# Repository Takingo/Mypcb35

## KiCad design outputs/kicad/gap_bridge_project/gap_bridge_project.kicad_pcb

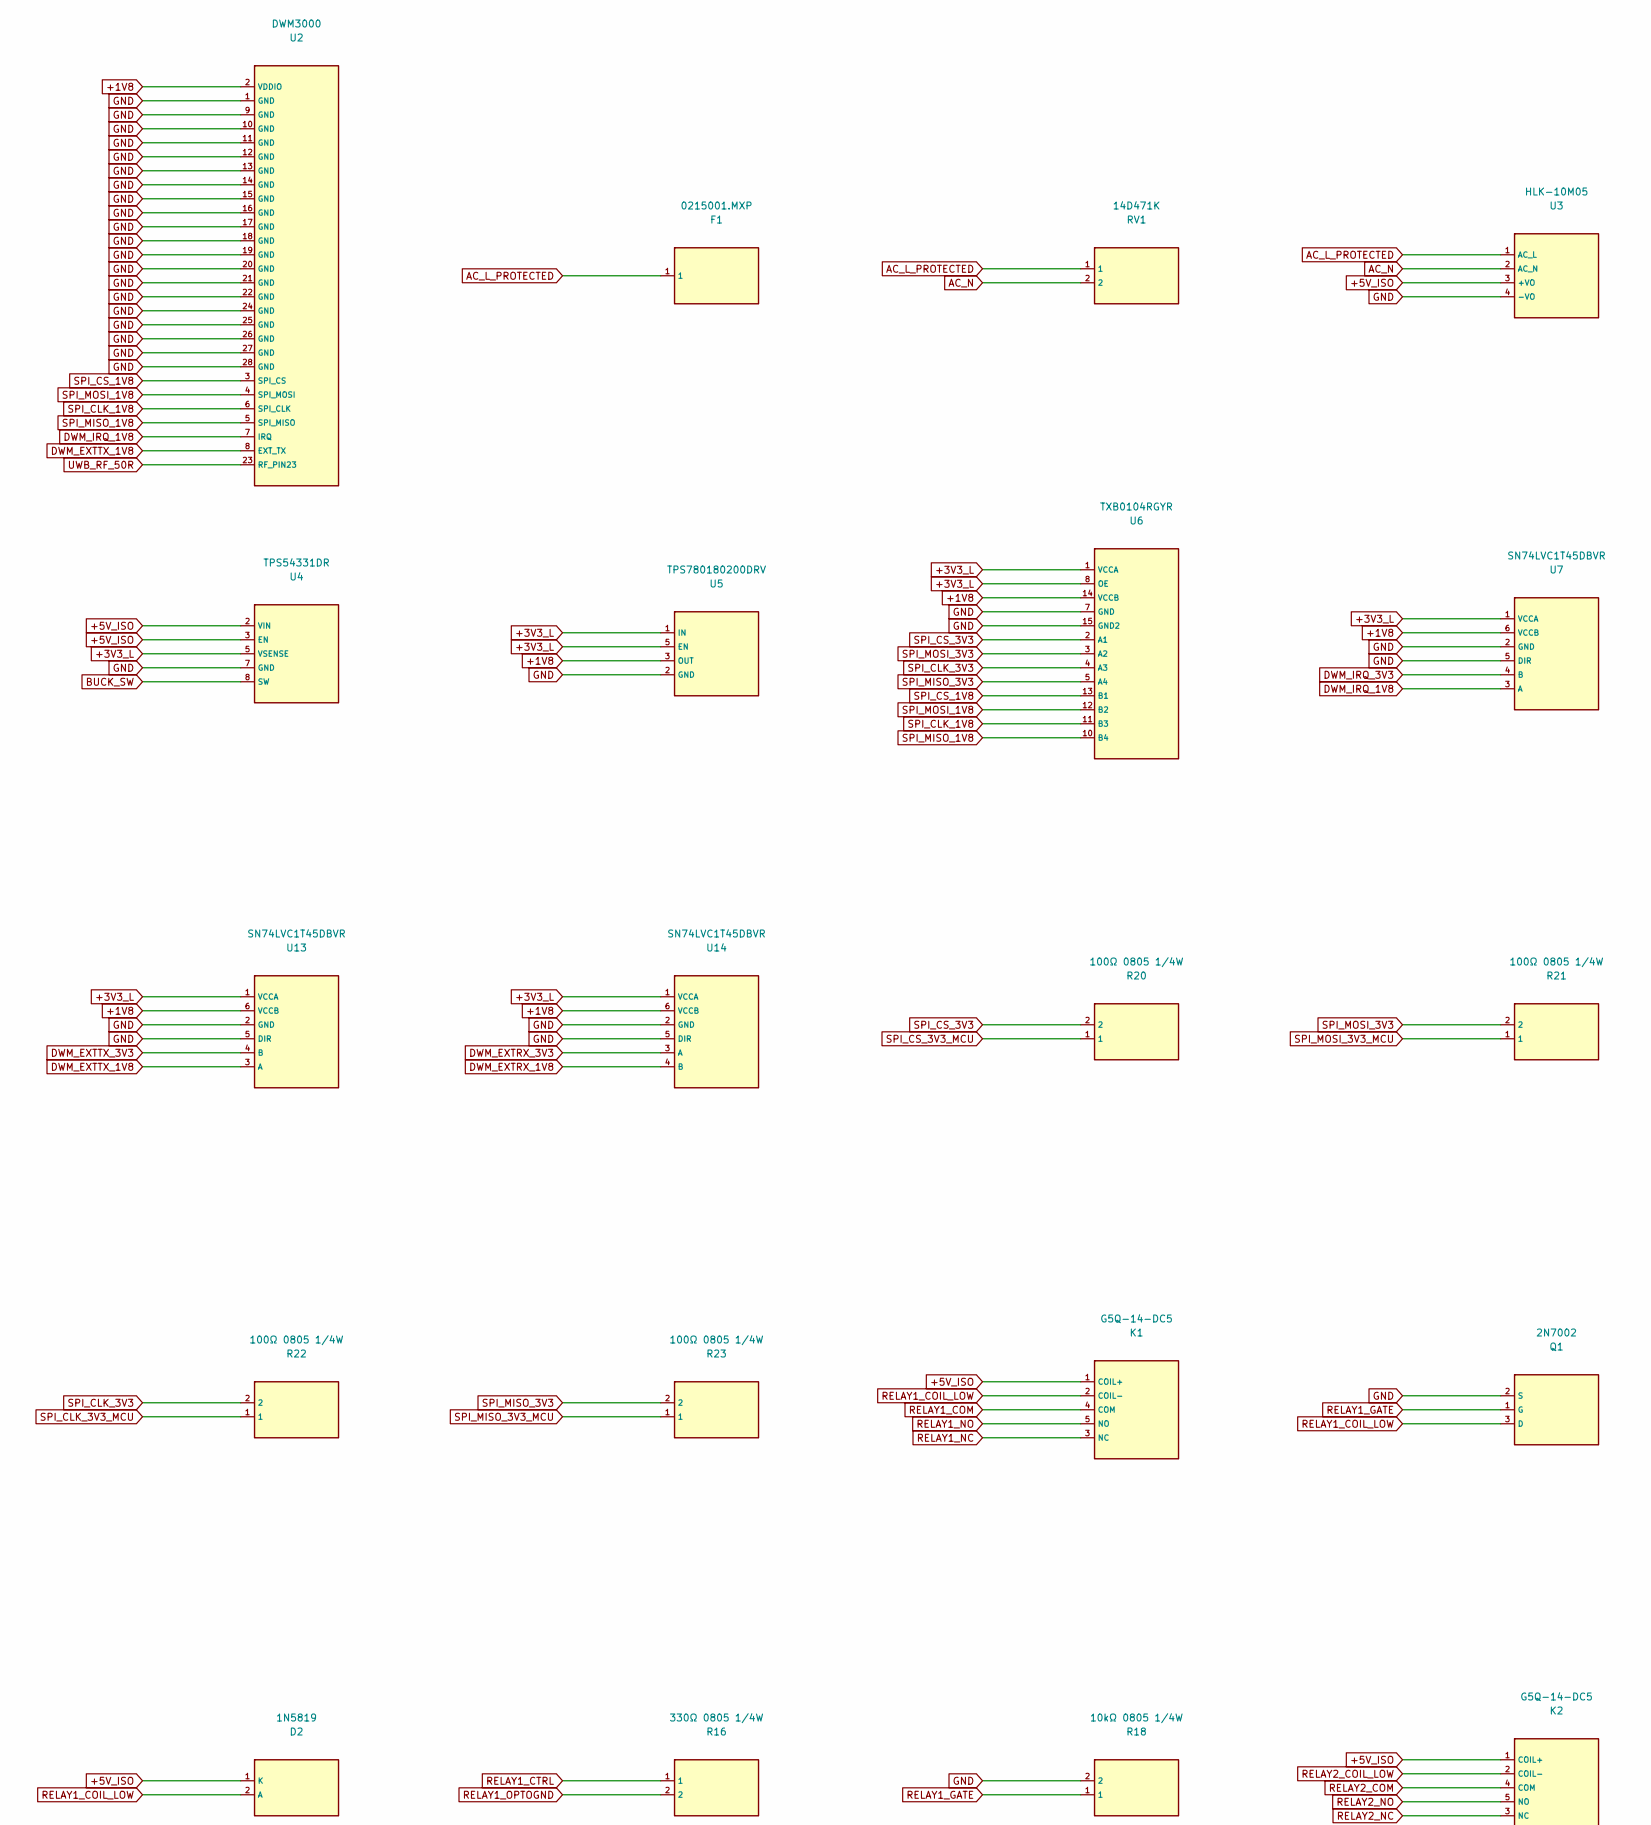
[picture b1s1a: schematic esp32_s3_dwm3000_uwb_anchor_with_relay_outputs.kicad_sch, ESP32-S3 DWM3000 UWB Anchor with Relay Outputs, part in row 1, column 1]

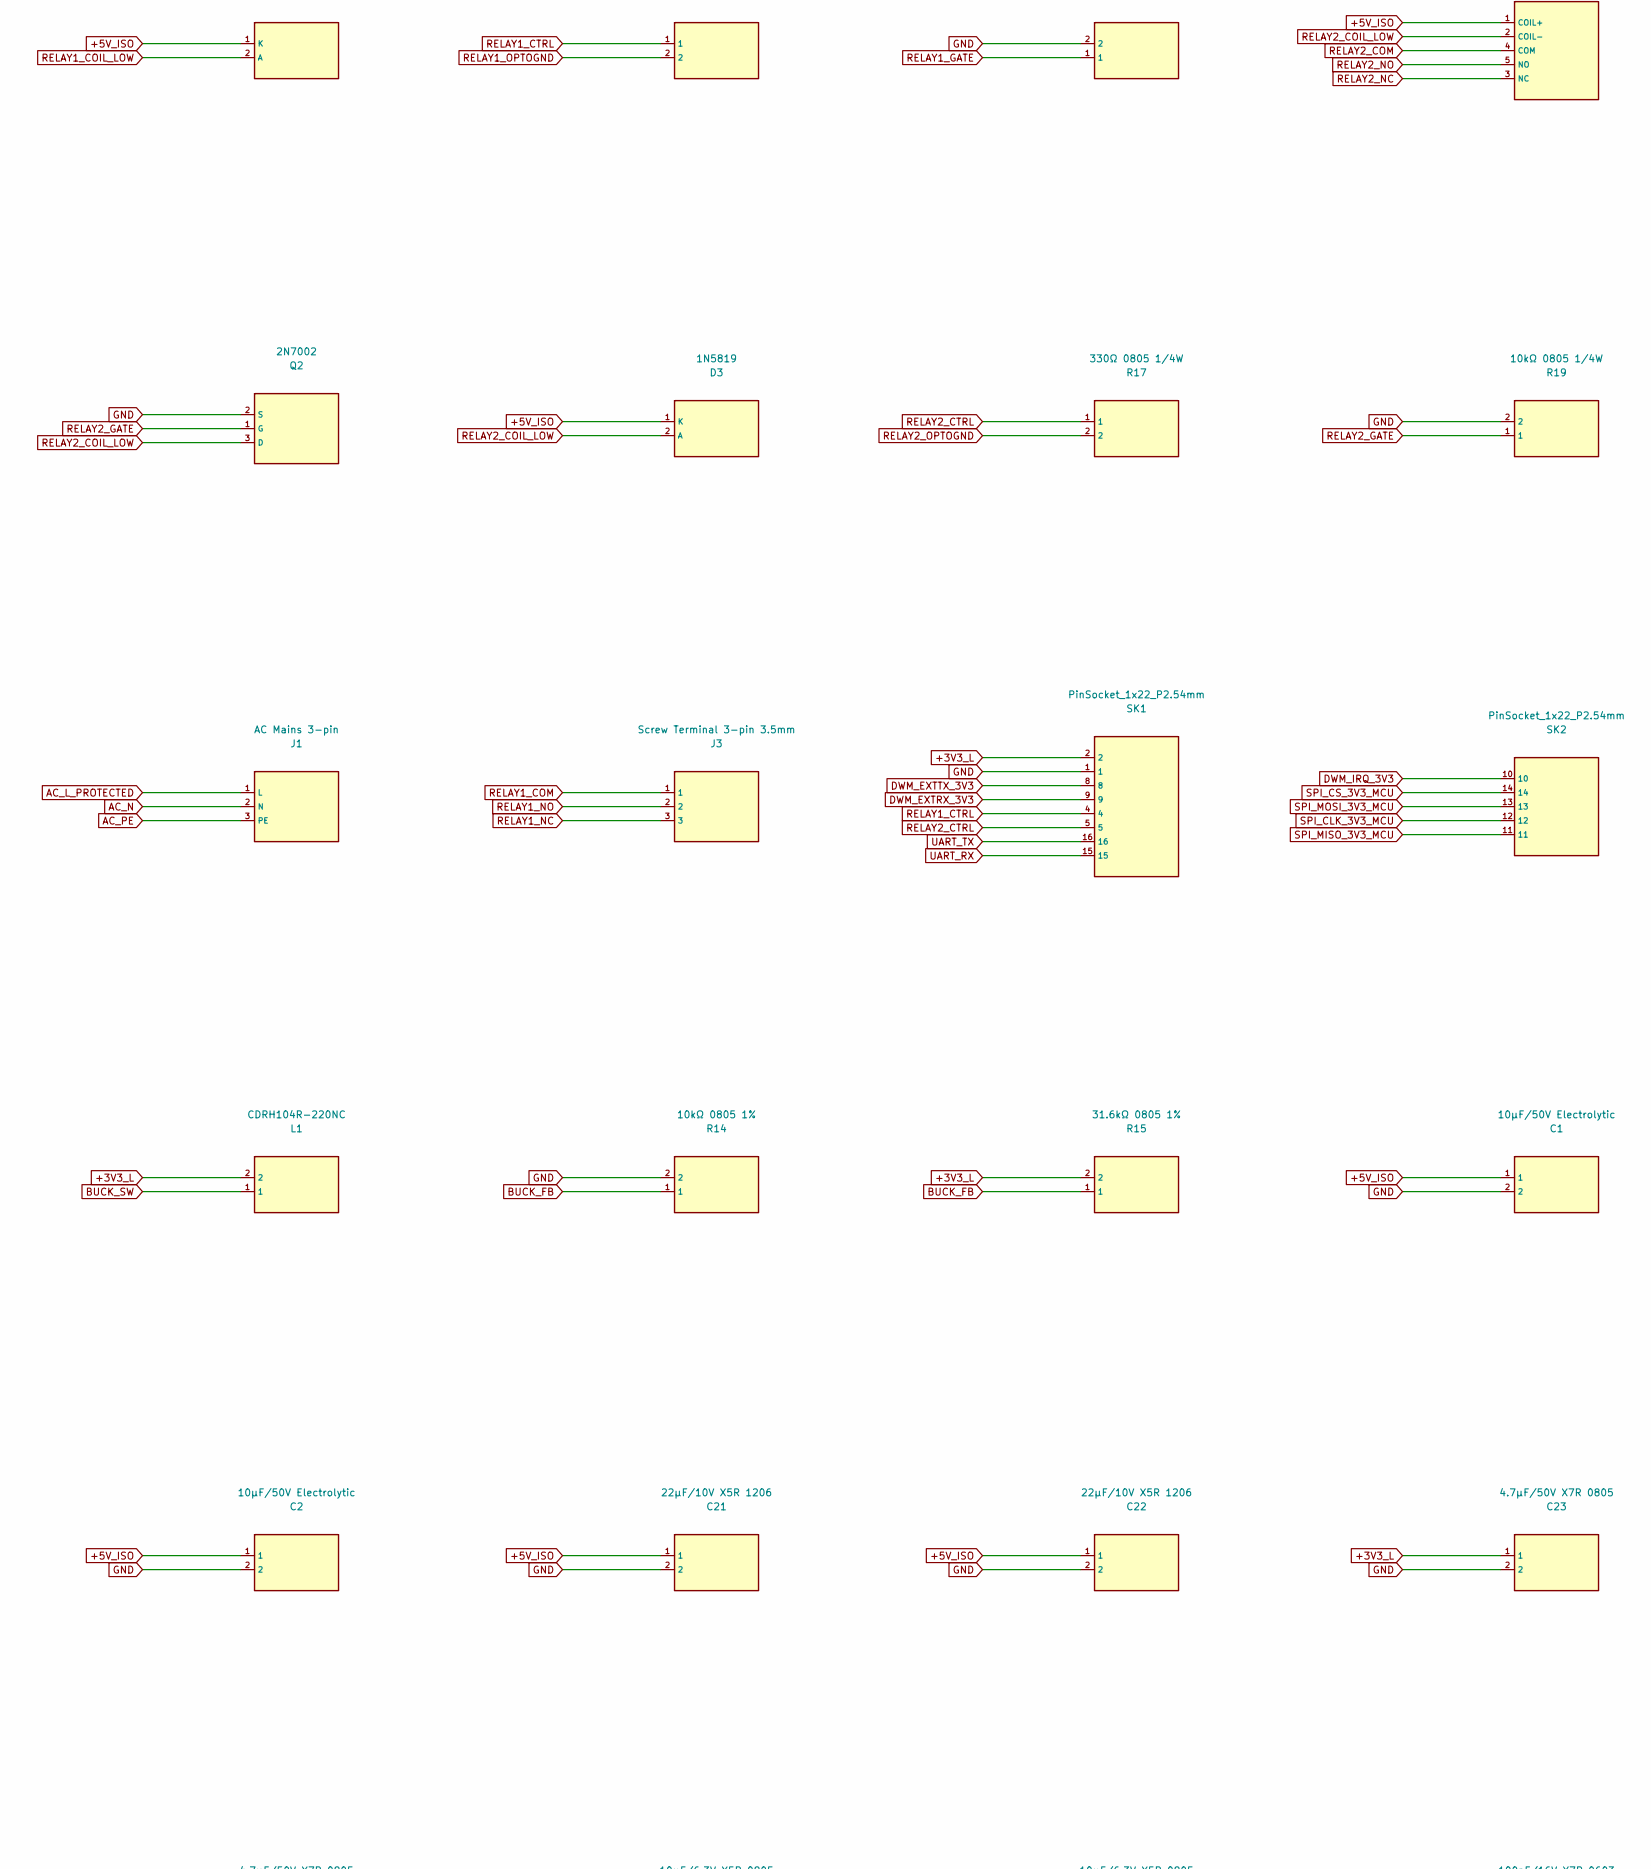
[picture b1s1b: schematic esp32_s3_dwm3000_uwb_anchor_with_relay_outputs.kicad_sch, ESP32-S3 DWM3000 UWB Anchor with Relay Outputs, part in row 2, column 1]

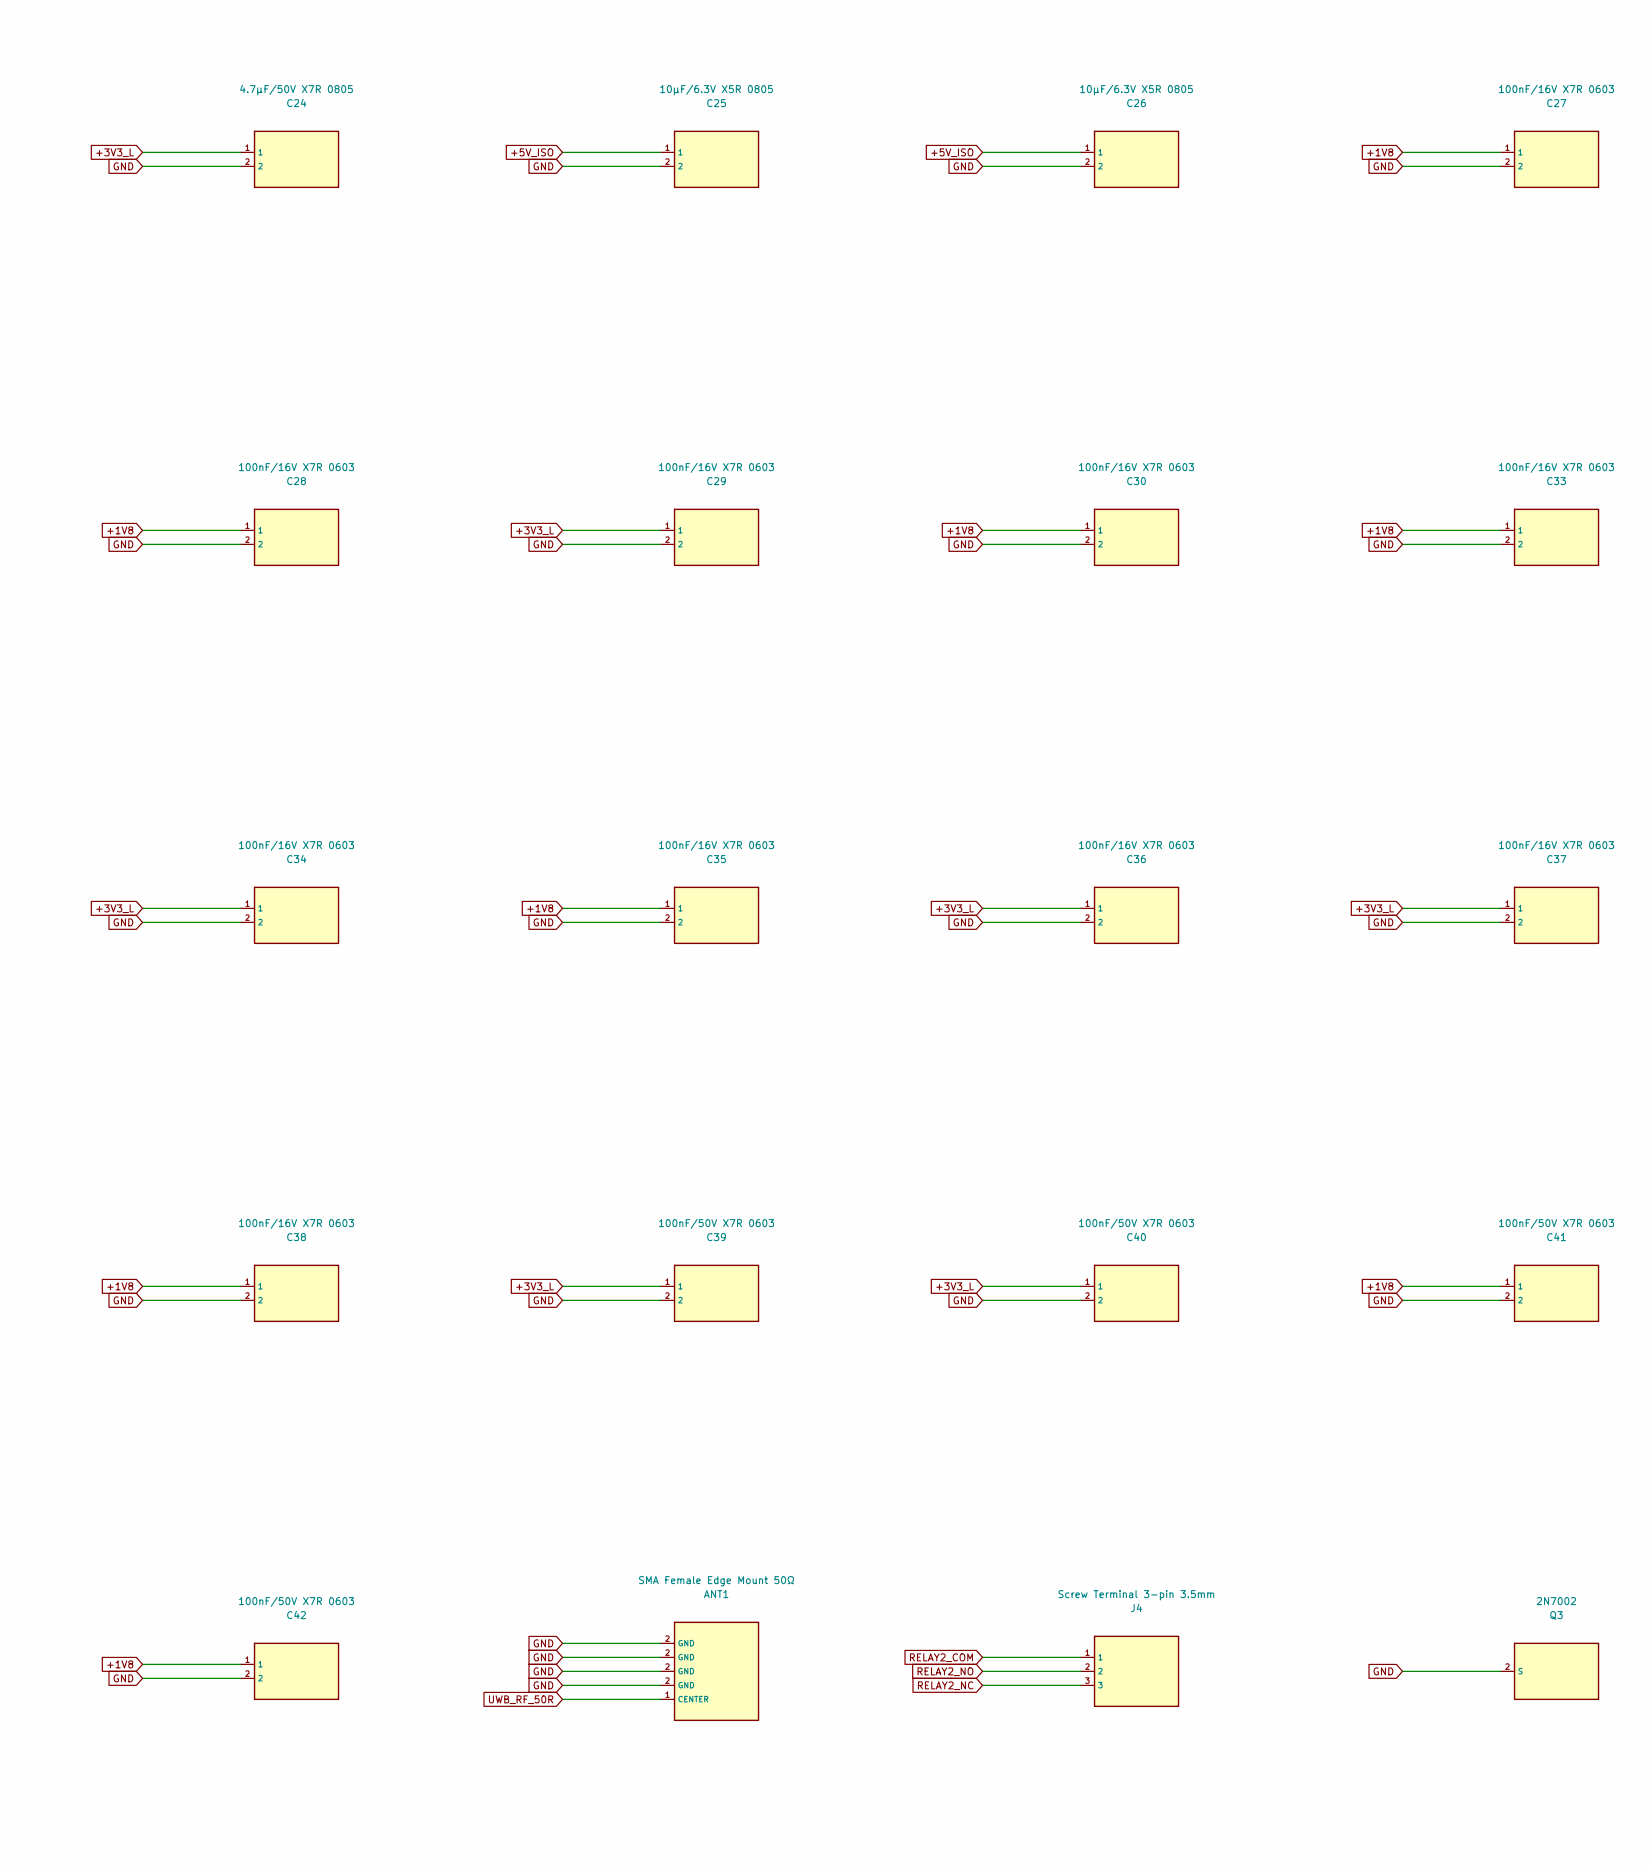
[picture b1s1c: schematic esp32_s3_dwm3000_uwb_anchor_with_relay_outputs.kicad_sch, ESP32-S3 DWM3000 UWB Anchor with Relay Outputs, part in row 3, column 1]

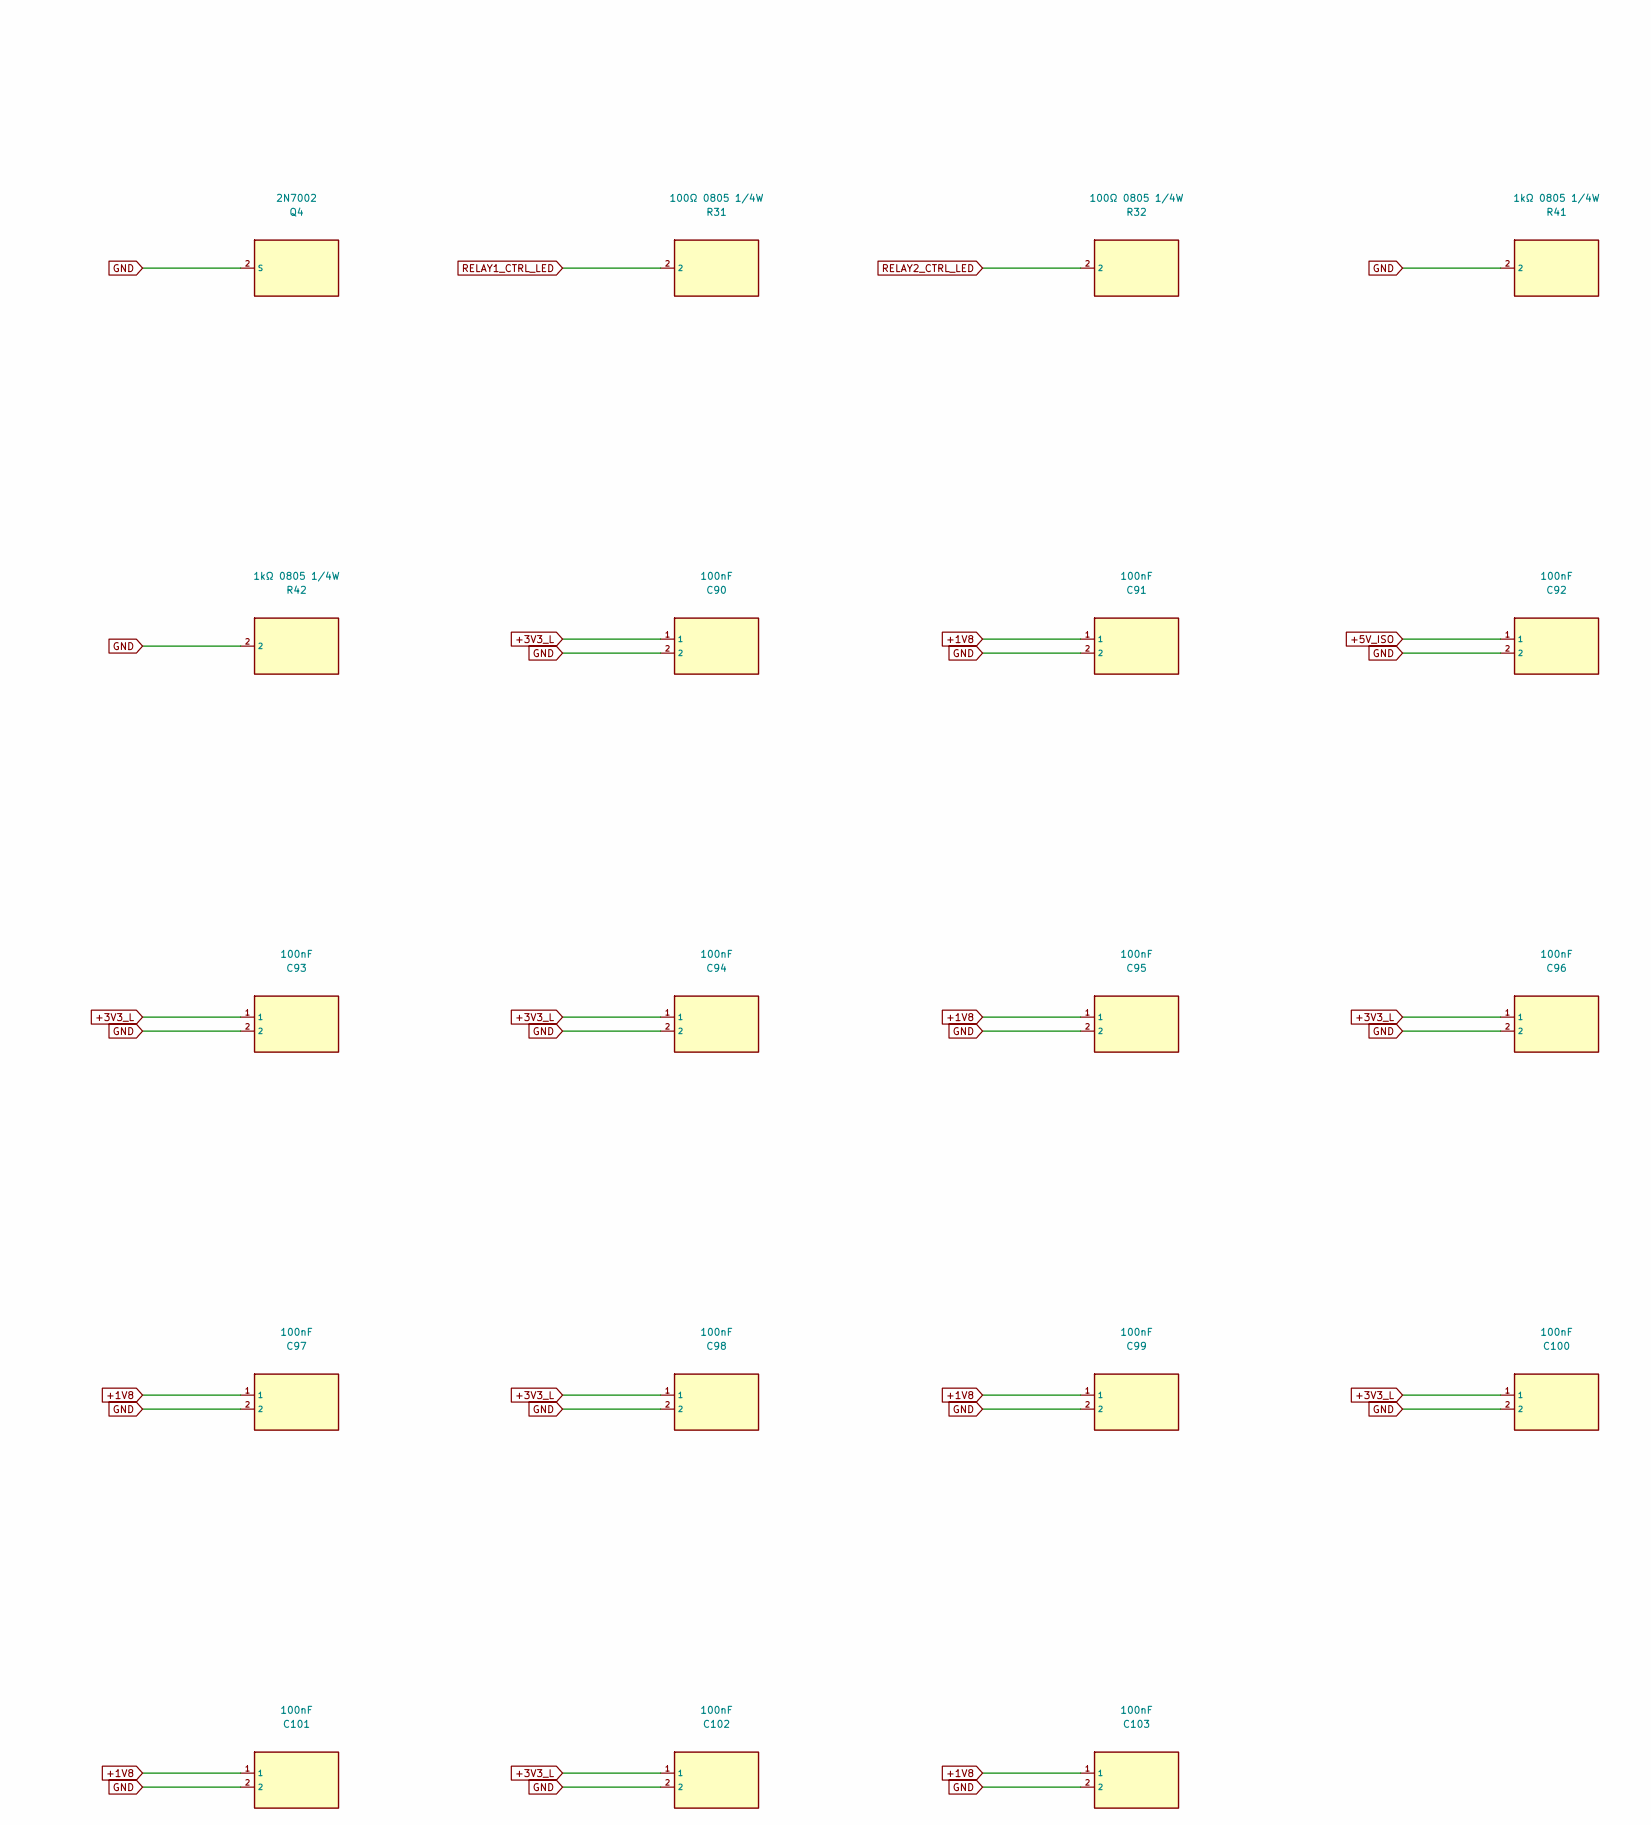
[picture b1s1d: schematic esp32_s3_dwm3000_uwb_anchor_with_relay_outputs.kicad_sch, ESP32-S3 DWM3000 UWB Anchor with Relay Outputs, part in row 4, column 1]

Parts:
ANT1: SMA Female Edge Mount 50Ω; SMA_Amphenol_132134_Vertical
C1, C2: 10µF/50V Electrolytic; CP_Radial_D5.0mm_P2.00mm
C21, C22: 22µF/10V X5R 1206; C_1206_3216Metric
C23, C24: 4.7µF/50V X7R 0805; C_0805_2012Metric
C25, C26: 10µF/6.3V X5R 0805; C_0805_2012Metric
C27, C28, C29, C30, C33, C34, C35, C36, C37, C38: 100nF/16V X7R 0603; C_0603_1608Metric
C39, C40, C41, C42: 100nF/50V X7R 0603; C_0603_1608Metric
C90, C91, C92, C93, C94, C95, C96, C97, C98, C99, C100, C101, C102, C103: 100nF; C_0603_1608Metric
D2, D3: 1N5819; D_SMA
F1: 0215001.MXP; Fuseholder_Littelfuse_100_series_5x20mm
J1: AC Mains 3-pin; TerminalBlock_Phoenix_PT-1,5-3-5.0-H_1x03_P5.00mm_Horizontal
J3, J4: Screw Terminal 3-pin 3.5mm; TerminalBlock_Phoenix_PT-1,5-3-3.5-H_1x03_P3.50mm_Horizontal
K1, K2: G5Q-14-DC5; Relay_SPDT_Omron-G5Q-1
L1: CDRH104R-220NC; L_10.4x10.4_H4.8
Q1, Q2, Q3, Q4: 2N7002; SOT-23
R14: 10kΩ 0805 1%; R_0805_2012Metric
R15: 31.6kΩ 0805 1%; R_0805_2012Metric
R16, R17: 330Ω 0805 1/4W; R_0805_2012Metric
R18, R19: 10kΩ 0805 1/4W; R_0805_2012Metric
R20, R21, R22, R23, R31, R32: 100Ω 0805 1/4W; R_0805_2012Metric
R41, R42: 1kΩ 0805 1/4W; R_0805_2012Metric
RV1: 14D471K; RV_Disc_D15.5mm_W4.5mm_P7.5mm
SK1, SK2: PinSocket_1x22_P2.54mm; PinSocket_1x22_P2.54mm_Vertical
U2: DWM3000
U3: HLK-10M05; Converter_ACDC_Hi-Link_HLK-10Mxx
U4: TPS54331DR; SOIC-8_3.9x4.9mm_P1.27mm
U5: TPS780180200DRV; SOT-23-5
U6: TXB0104RGYR; WQFN-14-1EP_2.5x2.5mm_P0.5mm_EP1.45x1.45mm
U7, U13, U14: SN74LVC1T45DBVR; SOT-23-6

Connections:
+1V8: C27.1, C28.1, C30.1, C33.1, C35.1, C38.1, C41.1, C42.1, C91.1, C95.1, C97.1, C99.1, C101.1, C103.1, U2.2 (VDDIO), U5.3 (OUT), U6.14 (VCCB), U7.6 (VCCB), U13.6 (VCCB), U14.6 (VCCB)
+3V3_L: C23.1, C24.1, C29.1, C34.1, C36.1, C37.1, C39.1, C40.1, C90.1, C93.1, C94.1, C96.1, C98.1, C100.1, C102.1, L1.2, R15.2, SK1.2, U4.5 (VSENSE), U5.1 (IN), U5.5 (EN), U6.1 (VCCA), U6.8 (OE), U7.1 (VCCA), U13.1 (VCCA), U14.1 (VCCA)
+5V_ISO: C1.1, C2.1, C21.1, C22.1, C25.1, C26.1, C92.1, D2.1 (K), D3.1 (K), K1.1 (COIL+), K2.1 (COIL+), U3.3 (+VO), U4.2 (VIN), U4.3 (EN)
AC_L_PROTECTED: F1.1, J1.1 (L), RV1.1, U3.1 (AC_L)
AC_N: J1.2 (N), RV1.2, U3.2 (AC_N)
AC_PE: J1.3 (PE)
BUCK_FB: R14.1, R15.1
BUCK_SW: L1.1, U4.8 (SW)
DWM_EXTRX_1V8: U14.4 (B)
DWM_EXTRX_3V3: SK1.9, U14.3 (A)
DWM_EXTTX_1V8: U2.8 (EXT_TX), U13.3 (A)
DWM_EXTTX_3V3: SK1.8, U13.4 (B)
DWM_IRQ_1V8: U2.7 (IRQ), U7.3 (A)
DWM_IRQ_3V3: SK2.10, U7.4 (B)
GND: ANT1.2 (GND), C1.2, C2.2, C21.2, C22.2, C23.2, C24.2, C25.2, C26.2, C27.2, C28.2, C29.2, C30.2, C33.2, C34.2, C35.2, C36.2, C37.2, C38.2, C39.2, C40.2, C41.2, C42.2, C90.2, C91.2, C92.2, C93.2, C94.2, C95.2, C96.2, C97.2, C98.2, C99.2, C100.2, C101.2, C102.2, C103.2, Q1.2 (S), Q2.2 (S), Q3.2, Q4.2, R14.2, R18.2, R19.2, R41.2, R42.2, SK1.1, U2.1 (GND), U2.9 (GND), U2.10 (GND), U2.11 (GND), U2.12 (GND), U2.13 (GND), U2.14 (GND), U2.15 (GND), U2.16 (GND), U2.17 (GND), U2.18 (GND), U2.19 (GND), U2.20 (GND), U2.21 (GND), U2.22 (GND), U2.24 (GND), U2.25 (GND), U2.26 (GND), U2.27 (GND), U2.28 (GND), U3.4 (-VO), U4.7 (GND), U5.2 (GND), U6.7 (GND), U6.15 (GND2), U7.2 (GND), U7.5 (DIR), U13.2 (GND), U13.5 (DIR), U14.2 (GND), U14.5 (DIR)
RELAY1_COIL_LOW: D2.2 (A), K1.2 (COIL-), Q1.3 (D)
RELAY1_COM: J3.1, K1.4 (COM)
RELAY1_CTRL: R16.1, SK1.4
RELAY1_CTRL_LED: R31.2
RELAY1_GATE: Q1.1 (G), R18.1
RELAY1_NC: J3.3, K1.3 (NC)
RELAY1_NO: J3.2, K1.5 (NO)
RELAY1_OPTOGND: R16.2
RELAY2_COIL_LOW: D3.2 (A), K2.2 (COIL-), Q2.3 (D)
RELAY2_COM: J4.1, K2.4 (COM)
RELAY2_CTRL: R17.1, SK1.5
RELAY2_CTRL_LED: R32.2
RELAY2_GATE: Q2.1 (G), R19.1
RELAY2_NC: J4.3, K2.3 (NC)
RELAY2_NO: J4.2, K2.5 (NO)
RELAY2_OPTOGND: R17.2
SPI_CLK_1V8: U2.6 (SPI_CLK), U6.11 (B3)
SPI_CLK_3V3: R22.2, U6.4 (A3)
SPI_CLK_3V3_MCU: R22.1, SK2.12
SPI_CS_1V8: U2.3 (SPI_CS), U6.13 (B1)
SPI_CS_3V3: R20.2, U6.2 (A1)
SPI_CS_3V3_MCU: R20.1, SK2.14
SPI_MISO_1V8: U2.5 (SPI_MISO), U6.10 (B4)
SPI_MISO_3V3: R23.2, U6.5 (A4)
SPI_MISO_3V3_MCU: R23.1, SK2.11
SPI_MOSI_1V8: U2.4 (SPI_MOSI), U6.12 (B2)
SPI_MOSI_3V3: R21.2, U6.3 (A2)
SPI_MOSI_3V3_MCU: R21.1, SK2.13
UART_RX: SK1.15
UART_TX: SK1.16
UWB_RF_50R: ANT1.1 (CENTER), U2.23 (RF_PIN23)

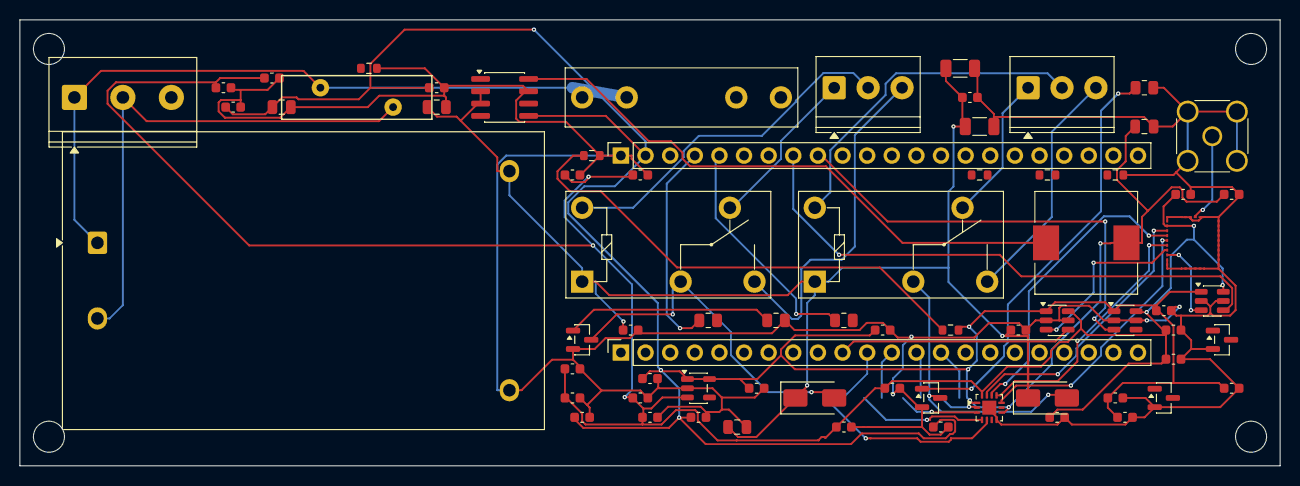
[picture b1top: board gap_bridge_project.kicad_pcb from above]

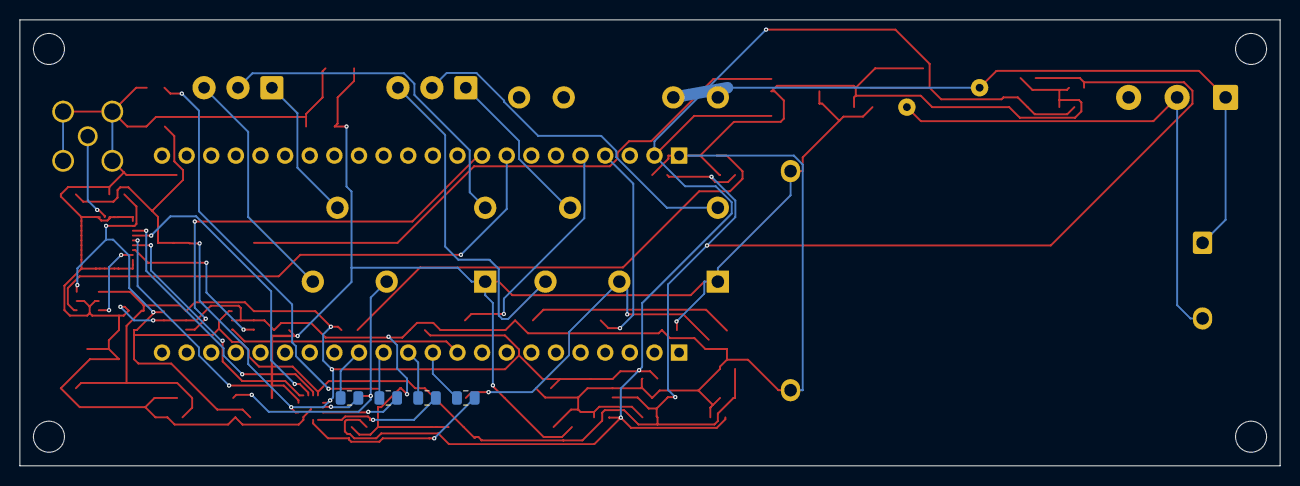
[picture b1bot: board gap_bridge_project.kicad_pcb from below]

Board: 4 copper layers, 130.0 x 46.0 mm, 75 parts (4 on the bottom side), 38 nets.

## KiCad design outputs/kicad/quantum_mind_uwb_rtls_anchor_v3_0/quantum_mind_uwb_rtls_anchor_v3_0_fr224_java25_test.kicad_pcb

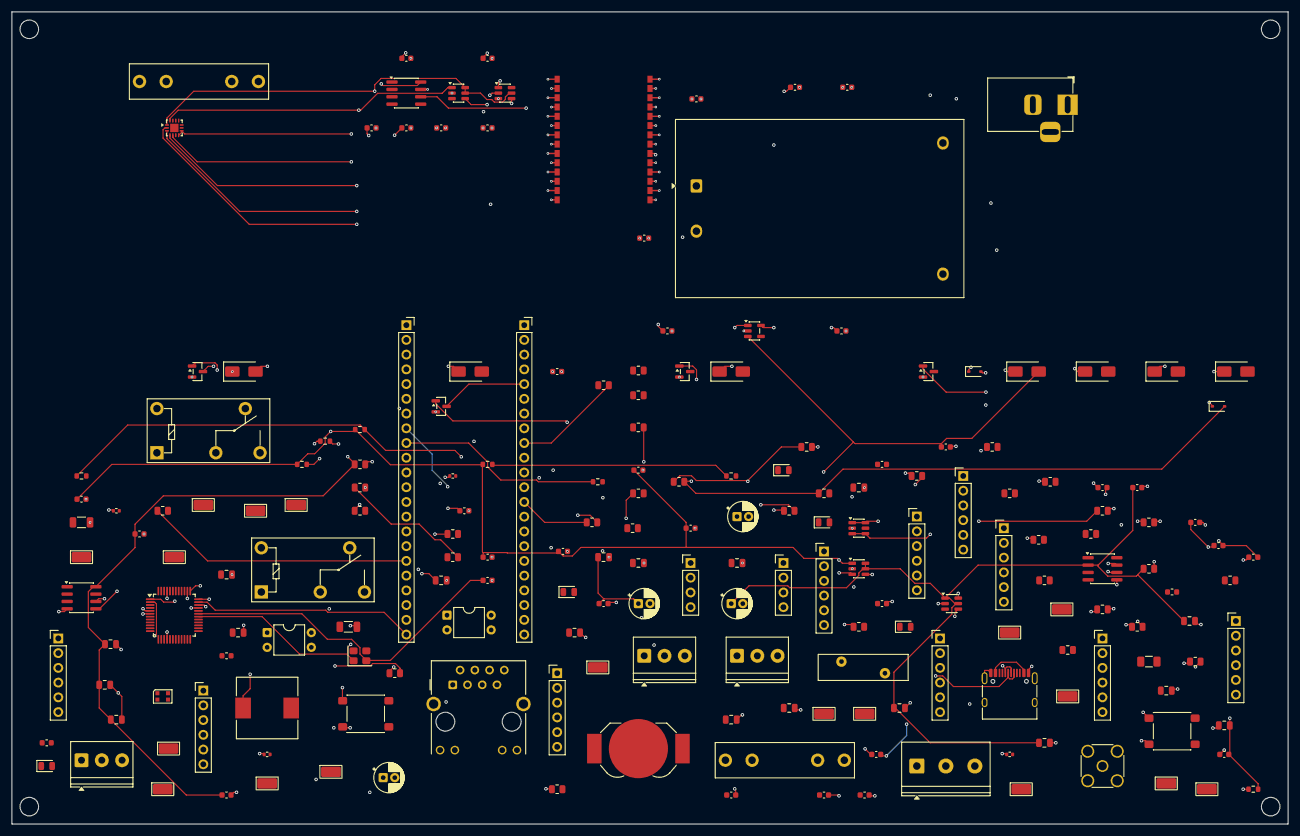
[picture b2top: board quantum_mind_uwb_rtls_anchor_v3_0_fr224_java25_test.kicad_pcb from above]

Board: 4 copper layers, 220.0 x 140.0 mm, 195 parts (0 on the bottom side), 65 nets.

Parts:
ANT1: SMA Female Edge Mount 50Ω; SMA_Amphenol_132134_Vertical
BAT1: CR2032 Holder SMD; BatteryHolder_LINX_BAT-HLD-012-SMT
C1, C2, C3, C4: 10µF/50V Electrolytic; CP_Radial_D5.0mm_P2.00mm
C5, C6, C7, C8, C9, C10, C11, C12: 100nF/50V X7R 0805; C_0805_2012Metric
C13, C14, C15, C16: 10µF/16V X5R 0805; C_0805_2012Metric
C17, C18, C19, C20: 1µF/16V X7R 0603; C_0603_1608Metric
C21, C22: 22µF/10V X5R 1206; C_1206_3216Metric
C23, C24: 4.7µF/50V X7R 0805; C_0805_2012Metric
C25, C26: 10µF/6.3V X5R 0805; C_0805_2012Metric
C27, C28, C29, C30, C33, C34, C35, C36, C37, C38: 100nF/16V X7R 0603; C_0603_1608Metric
C31: 330pF/50V C0G 0603; C_0603_1608Metric
C32: 100pF/50V C0G 0603; C_0603_1608Metric
C39, C40, C41, C42: 100nF/50V X7R 0603; C_0603_1608Metric
C43, C44: 10µF/25V X5R 0805; C_0805_2012Metric
C90, C91, C92, C93, C94, C95, C96, C97, C98, C99, C100, C101, C102: 100nF; C_0603_1608Metric
C_X1A, C_X1A-C_X1B, C_X1B: 18pF/50V C0G 0603; C_0603_1608Metric
D1: SS34-E3/57T; D_SMA
D2, D3: 1N5819; D_SMA
D4, D5: 1N4148TR; D_SOD-323
D6, D7, D8: SMBJ3.3A; D_SMA
D9: SMBJ1.8A; D_SMA
D10: USBLC6-2SC6; SOT-23-6
F1: 0215001.MXP; Fuseholder_Littelfuse_100_series_5x20mm
F2: 0ZCJ0050FF2G; Fuse_1206_3216Metric
FB1, FB2, FB3: BLM18PG221SN1D; L_0603_1608Metric
J1_AC: Screw Terminal 3-pin 5.0mm; TerminalBlock_Phoenix_PT-1,5-3-5.0-H_1x03_P5.00mm_Horizontal
J1_USB: USB Type-C Receptacle 16-pin; USB_C_Receptacle_HRO_TYPE-C-31-M-12
J2: DC Power Jack 5.5×2.1mm; BarrelJack_Horizontal
J3, J4, J5: Screw Terminal 3-pin 3.5mm; TerminalBlock_Phoenix_PT-1,5-3-3.5-H_1x03_P3.50mm_Horizontal
J6, J7, J8, J9, J10, J11, J12, J13, J16, J17: Pin Header 1×6 2.54mm Male; PinHeader_1x06_P2.54mm_Vertical
J14, J15: Pin Header 1×4 2.54mm Male; PinHeader_1x04_P2.54mm_Vertical
J18: HR911105A; RJ45_Hanrun_HR911105A_Horizontal
J_FUSE: Fuse Holder 5×20mm PCB; Fuseholder_Littelfuse_100_series_5x20mm
K1, K2: G5Q-14-DC5; Relay_SPDT_Omron-G5Q-1
L1: CDRH104R-220NC; L_10.4x10.4_H4.8
LED1, LED5: Green LED 0805; LED_0805_2012Metric
LED2: Blue LED 0805; LED_0805_2012Metric
LED3: Red LED 0805; LED_0805_2012Metric
LED4: Yellow LED 0805; LED_0805_2012Metric
LED6: WS2812B-2020; LED_WS2812B-2020_PLCC4_2.0x2.0mm
Q1, Q2, Q3, Q4: 2N7002; SOT-23
R1, R1-R3R_LED4R_LED5, R2, R3: 220Ω 0805 1/4W; R_0805_2012Metric
R6, R7, R8, R9, R18, R19, R28, R29, R30, R34: 10kΩ 0805 1/4W; R_0805_2012Metric
R10, R11, R41, R42: 1kΩ 0805 1/4W; R_0805_2012Metric
R12, R13: 4.7kΩ 0805 1/4W; R_0805_2012Metric
R14: 10kΩ 0805 1%; R_0805_2012Metric
R15: 31.6kΩ 0805 1%; R_0805_2012Metric
R16, R17: 330Ω 0805 1/4W; R_0805_2012Metric
R20, R21, R22, R23, R31, R32: 100Ω 0805 1/4W; R_0805_2012Metric
R33: 0Ω 0805; R_0805_2012Metric
R35, R36, R37: 10kΩ 0603 1/8W; R_0603_1608Metric
R38, R39, R40: 100Ω 0603 1/8W; R_0603_1608Metric
R43, R44, R45, R46: 49.9Ω 0402 1%; R_0402_1005Metric
R47: 470Ω 0805 1/4W; R_0805_2012Metric
RV1: 14D471K; RV_Disc_D15.5mm_W4.5mm_P7.5mm
R_LED4, R_LED5: 220Ω 0805 1/4W; R_0805_2012Metric
R_RST1, R_RST2: 10kΩ 0603 1/8W; R_0603_1608Metric
R_WDG: 100kΩ 0805 1/4W; R_0805_2012Metric
SK1, SK2: PinSocket_1x22_P2.54mm; PinSocket_1x22_P2.54mm_Vertical
SW1, SW2: Tactile Switch 6×6mm SMD; SW_SPST_PTS645Sx43SMTR92
TP1, TP2, TP3, TP4, TP5, TP6, TP7, TP8, TP9, TP10, TP11, TP12, TP13, TP14, TP15, TP16, TP17, TP18: Test Point SMD 1.27mm Red; TestPoint_Keystone_5015_Micro_Mini
U2: DWM3000
U3: HLK-10M05; Converter_ACDC_Hi-Link_HLK-10Mxx
U4: TPS54331DR; SOIC-8_3.9x4.9mm_P1.27mm
U5: TPS780180200DRV; SOT-23-5
U6: TXB0104RGYR; WQFN-14-1EP_2.5x2.5mm_P0.5mm_EP1.45x1.45mm
U7, U13, U14: SN74LVC1T45DBVR; SOT-23-6
U8: TPL5010DDCR; SOT-23-6
U9: DS3231SN; SOIC-8_3.9x4.9mm_P1.27mm
U10: AT24C256C-SSHL; SOIC-8_3.9x4.9mm_P1.27mm
U11, U12: PC817X2CSP9F; DIP-4_W7.62mm
U15: W5500; LQFP-48_7x7mm_P0.5mm
X1: 25MHz / 18pF; Crystal_SMD_3225-4Pin_3.2x2.5mm

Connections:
1V8_DWM: C17.1, C18.1, C19.1, C20.1, C27.1, C28.1, C30.1, C33.1, C35.1, C38.1, D9.2, R35.1, R36.1, R37.1, U5.3, U6.14, U7.1, U13.1, U14.6
3V3_MAIN: C3.1, C4.1, C6.1, C7.1, C8.1, C9.1, C10.1, C23.1, C24.1, C29.1, C34.1, C36.1, C37.1, R28.1, R29.1, R30.1, R34.1, U5.1, U6.1, U7.5, U7.6, U8.5, U9.2, U10.8, U13.5, U13.6, U14.1, U14.5
5V_MAIN: C1.1, C2.1
5V_USB: J1_USB.A4, J1_USB.A9, J1_USB.B4, J1_USB.B9
5V_USB_FILTERED: SK1.1, SK2.1
+1V8: C92.1, C94.1, C96.1, C98.1, C102.1
+3V3: C90.1, C91.1, C93.1, C95.1, C97.1, C100.1, C101.1
+5V_ISO: C99.1, D1.1, D2.1, D3.1, D4.1, D5.1, D6.1, D7.1, D8.1, D9.1, K1.1, K2.1
AC_L: J1_AC.1, RV1.1, U3.1
AC_N: J1_AC.2, RV1.2, U3.2
GND: ANT1.2, C1.2, C2.2, C3.2, C4.2, C5.2, C6.2, C7.2, C8.2, C9.2, C10.2, C11.2, C12.2, C13.2, C14.2, C15.2, C16.2, C17.2, C18.2, C19.2, C20.2, C21.2, C22.2, C23.2, C24.2, C25.2, C26.2, C27.2, C28.2, C29.2, C30.2, C31.2, C32.2, C33.2, C34.2, C35.2, C36.2, C37.2, C38.2, C39.2, C40.2, C41.2, C42.2, C43.2, C44.2, C90.2, C91.2, C92.2, C93.2, C94.2, C95.2, C96.2, C97.2, C98.2, C99.2, C100.2, C101.2, C102.2, C_X1A.2, C_X1B.2, D10.2, J1_USB.A1, J1_USB.A12, J1_USB.B1, J1_USB.B12, J1_USB.SH, J2.2, J2.3, J18.SH, Q1.2, Q2.2, Q3.2, Q4.2, R14.2, R18.2, R19.2, R_RST2.2, R_WDG.2, SK1.2, SK1.10, SK1.11, SK1.13, SK1.14, SK2.2, SK2.3, SK2.4, SK2.16, SK2.17, SK2.18, SK2.19, SK2.20, SK2.21, SK2.22, SW1.2, SW2.2, U2.1, U2.2, U2.3, U2.4, U2.5, U2.6, U2.7, U2.8, U2.9, U2.10, U2.11, U2.12, U2.13, U2.14, U2.15, U2.16, U2.17, U2.18, U2.19, U2.20, U2.21, U2.22, U2.23, U2.24, U2.25, U2.26, U2.27, U2.28, U3.4, U4.7, U5.2, U6.7, U6.8, U7.2, U8.3, U9.5, U10.4, U13.2, U14.2, U15.16
NET_DWM3000_DEBUGOUT_1V8: R37.2, R40.1
NET_DWM3000_EXT_RX_1V8: R35.2, U14.4
NET_DWM3000_EXT_TX_1V8_SERIES: R36.2, R39.1, U13.3
NET_DWM3000_RSTN_1V65: R_RST1.2, R_RST2.1
NET_DWM3000_SPI_CLK_3V3_SERIES: R20.2, U6.2
NET_DWM3000_SPI_CS_3V3_SERIES: R23.2, U6.5
NET_DWM3000_SPI_MISO_3V3_SERIES: R22.2, U6.4
NET_DWM3000_SPI_MOSI_3V3_SERIES: R21.2, U6.3
NET_ESP32_EN: D5.2, Q1.3, R28.2, R47.1, SK1.3, SW1.1, U8.4
NET_ESP32_EXT_RX: R38.1, SK1.9
NET_ESP32_EXT_TX: SK1.8, U13.4
NET_ESP32_GPIO0: D4.2, Q2.3, R29.2, SK2.5, SW2.1
NET_ESP32_GPIO1: R_LED4.1, SK1.17
NET_ESP32_GPIO2: R_LED5.1, SK1.18
NET_ESP32_GPIO4: R16.1, SK1.4
NET_ESP32_GPIO5: R17.1, SK1.5
NET_ESP32_GPIO6: R2.1, SK1.6
NET_ESP32_GPIO7: R3.1, SK1.7
NET_ESP32_GPIO8: C11.1, SK1.12
NET_ESP32_GPIO9: R_RST1.1, SK2.15
NET_ESP32_GPIO45: R30.2, SK2.6, U8.2
NET_ESP32_IRQ: SK2.10, U7.4
NET_ESP32_SPI_CLK: R20.1, SK2.14
NET_ESP32_SPI_CS: R23.1, SK2.11
NET_ESP32_SPI_MISO: R22.1, SK2.12
NET_ESP32_SPI_MOSI: R21.1, SK2.13
NET_I2C_SCL: R13.2, U9.7, U10.6
NET_I2C_SDA: R12.2, SK2.9, U9.6, U10.5
NET_U4_COMP: C31.1, C32.1, U4.6
NET_U4_FB: R14.1, R15.2
NET_U4_SW: D1.2, L1.1, U4.8
NET_U5_EN: R34.2, U5.5
NET_U8_DELAY: R_WDG.1, U8.1
NET_U11_COLLECTOR: Q3.1, R18.1
NET_U12_COLLECTOR: Q4.1, R19.1
NET_USB_DTR: Q1.1, R31.1
NET_USB_D_N: D10.3, D10.4, J1_USB.A7, J1_USB.B7
NET_USB_D_P: D10.1, D10.6, J1_USB.A6, J1_USB.B6
NET_USB_RTS: Q2.1, R32.1
NET_W5500_INT: R42.1, SK2.7
NET_W5500_INTn: R42.2, U15.38
NET_W5500_REGD: C44.1, U15.45
NET_W5500_RST: R41.1, SK2.8
NET_W5500_RX_N: J18.6, R46.1, U15.6
NET_W5500_RX_P: J18.3, R45.1, U15.5
NET_W5500_SPI2_CLK: SK1.22, U15.35
NET_W5500_SPI2_CS: SK1.19, U15.36
NET_W5500_SPI2_MISO: SK1.20, U15.34
NET_W5500_SPI2_MOSI: SK1.21, U15.33
NET_W5500_TX_N: J18.2, R44.1, U15.1
NET_W5500_TX_P: J18.1, R43.1, U15.2
NET_W5500_XTAL_IN: C_X1A.1, U15.30, X1.1
NET_W5500_XTAL_OUT: C_X1B.1, U15.31, X1.2
NET_W5500_nRESET: R41.2, U15.37
